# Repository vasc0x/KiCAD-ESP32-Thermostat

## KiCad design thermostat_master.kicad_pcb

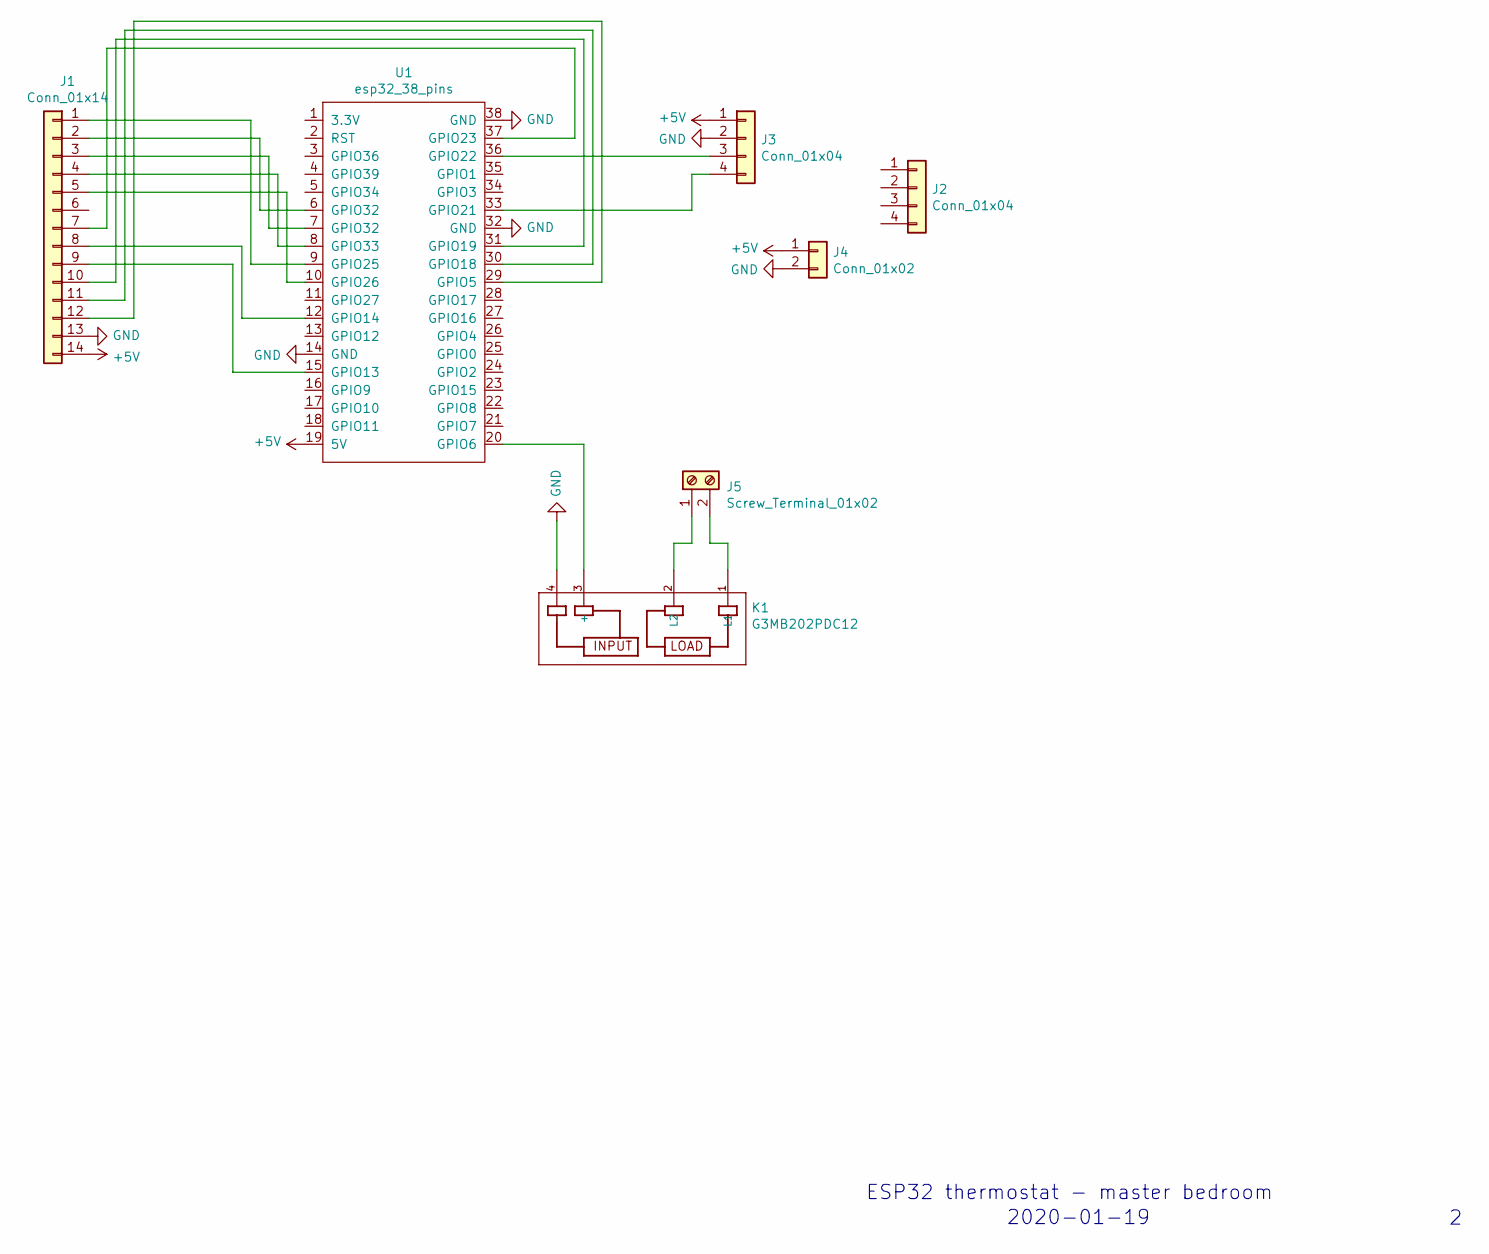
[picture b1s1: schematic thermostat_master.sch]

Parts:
J1: Conn_01x14; PinHeader_1x14_P2.54mm_Vertical
J2, J3: Conn_01x04; PinHeader_1x04_P2.54mm_Vertical
J4: Conn_01x02; PinHeader_1x02_P2.54mm_Vertical
J5: Screw_Terminal_01x02; TerminalBlock_bornier-2_P5.08mm
K1: G3MB202PDC12; RELAY_G3MB202PDC12
U1: esp32_38_pins; ESP32_Keeyes_38_Pins

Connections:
+5V: J1.14, J3.1, J4.1, U1.19 (5V)
GND: J1.13, J3.2, J4.2, K1.4 (-), U1.14 (GND), U1.32 (GND), U1.38 (GND)
unnamed: J1.1, U1.9 (GPIO25)
unnamed: J1.2, U1.6 (GPIO32)
unnamed: J1.3, U1.7 (GPIO32)
unnamed: J1.4, U1.8 (GPIO33)
unnamed: J1.5, U1.10 (GPIO26)
unnamed: J1.7, U1.37 (GPIO23)
unnamed: J1.8, U1.12 (GPIO14)
unnamed: J1.9, U1.15 (GPIO13)
unnamed: J1.10, U1.31 (GPIO19)
unnamed: J1.11, U1.30 (GPIO18)
unnamed: J1.12, U1.29 (GPIO5)
unnamed: J3.3, U1.36 (GPIO22)
unnamed: J3.4, U1.33 (GPIO21)
unnamed: J5.1, K1.2 (L2)
unnamed: J5.2, K1.1 (L1)
unnamed: K1.3 (+), U1.20 (GPIO6)

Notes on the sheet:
ESP32 thermostat - master bedroom
2020-01-19

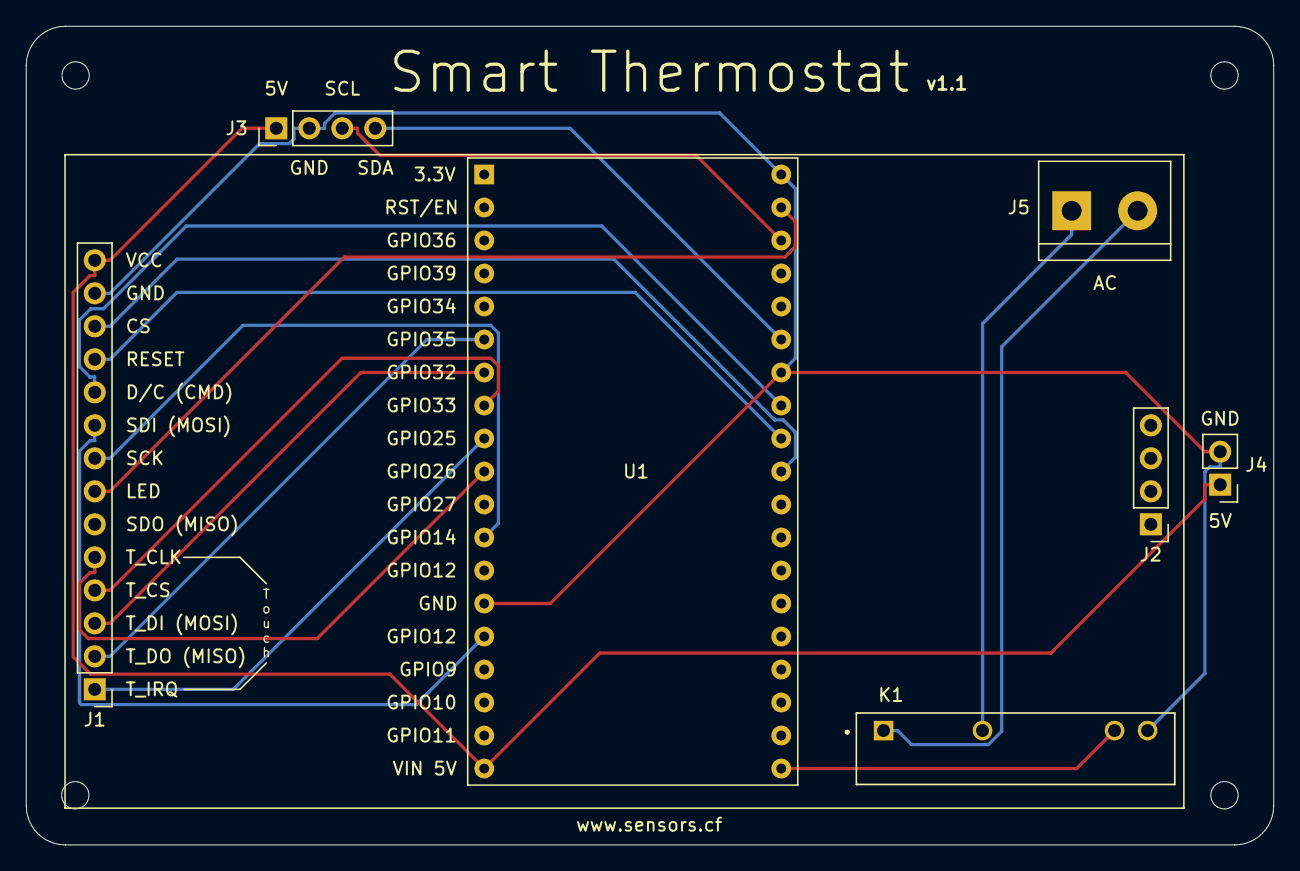
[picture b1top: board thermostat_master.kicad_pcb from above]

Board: 2 copper layers, 96.0 x 63.0 mm, 7 parts (0 on the bottom side), 18 nets.

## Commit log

2020-01-22 add files
2020-02-15 v1.1 PCB
